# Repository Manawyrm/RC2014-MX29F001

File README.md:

# MX29F001B 128KiB Flash board

PCB tested & working, needs 74HCT32 chip  
Maps 8k of ROM into the start of the address space  
  
Gerbers available in gerber/-Folder

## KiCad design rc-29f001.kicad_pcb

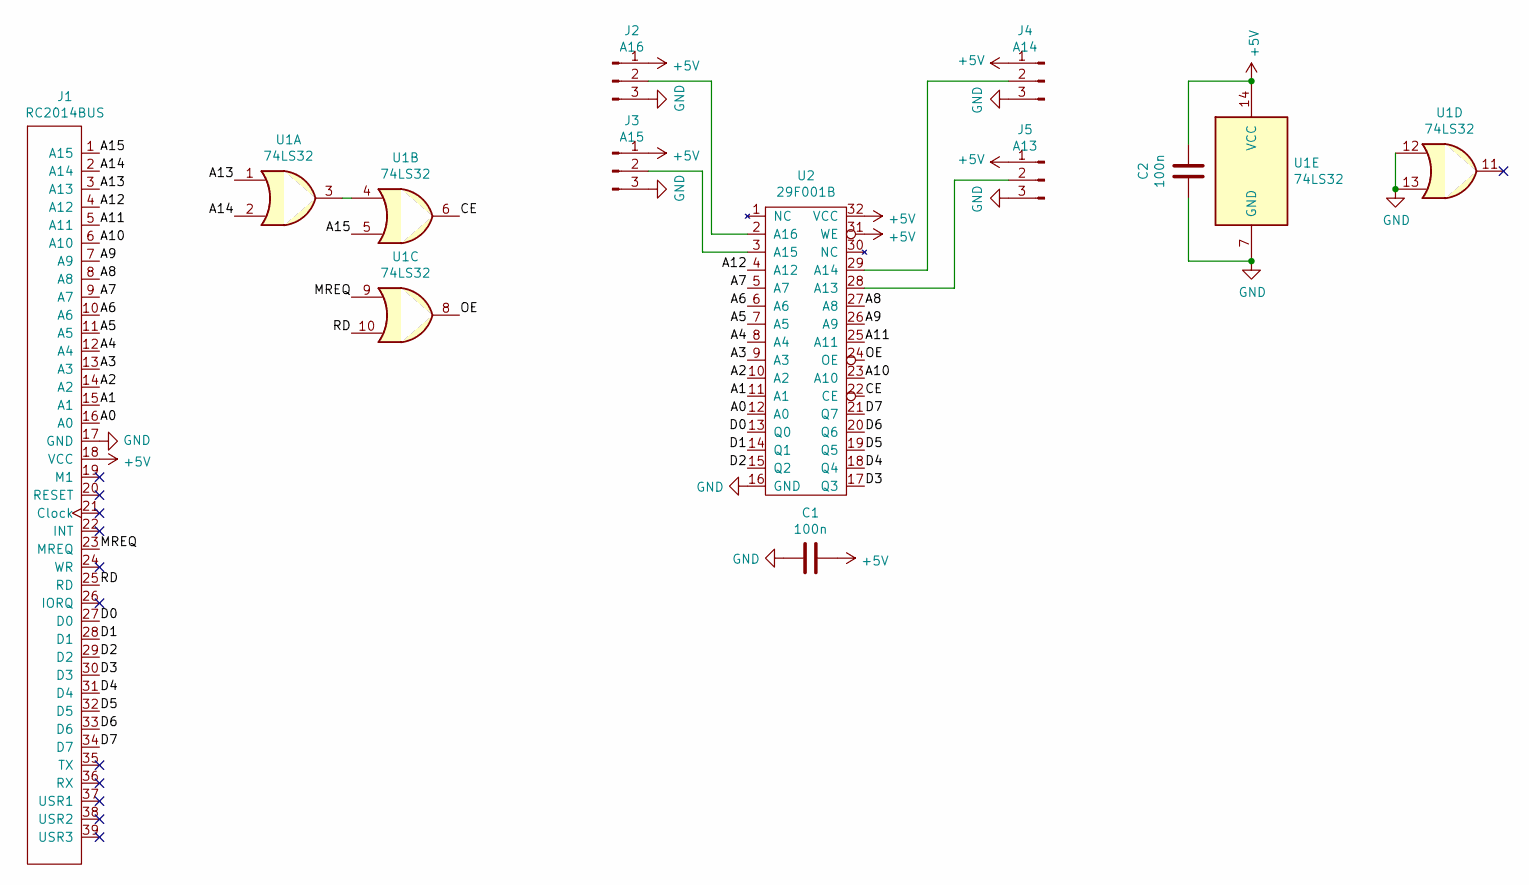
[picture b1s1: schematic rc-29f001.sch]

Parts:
C1, C2: 100n; C_0805_HandSoldering
J1: RC2014BUS; PinHeader_1x39_P2.54mm_Vertical
J2: A16; Pin_Header_Straight_1x03_Pitch2.54mm
J3: A15; Pin_Header_Straight_1x03_Pitch2.54mm
J4: A14; Pin_Header_Straight_1x03_Pitch2.54mm
J5: A13; Pin_Header_Straight_1x03_Pitch2.54mm
U1: 74LS32; DIP-14_W7.62mm_Socket_LongPads
U2: 29F001B; DIP-32_W15.24mm_Socket_LongPads

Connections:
+5V: C1.1, C2.1, J1.18 (VCC), J2.1, J3.1, J4.1, J5.1, U1.14 (VCC), U2.31 (WE), U2.32 (VCC)
/A0: J1.16 (A0), U2.12 (A0)
/A1: J1.15 (A1), U2.11 (A1)
/A2: J1.14 (A2), U2.10 (A2)
/A3: J1.13 (A3), U2.9 (A3)
/A4: J1.12 (A4), U2.8 (A4)
/A5: J1.11 (A5), U2.7 (A5)
/A6: J1.10 (A6), U2.6 (A6)
/A7: J1.9 (A7), U2.5 (A7)
/A8: J1.8 (A8), U2.27 (A8)
/A9: J1.7 (A9), U2.26 (A9)
/A10: J1.6 (A10), U2.23 (A10)
/A11: J1.5 (A11), U2.25 (A11)
/A12: J1.4 (A12), U2.4 (A12)
/A13: J1.3 (A13), U1.1
/A14: J1.2 (A14), U1.2
/A15: J1.1 (A15), U1.5
/CE: U1.6, U2.22 (CE)
/D0: J1.27 (D0), U2.13 (Q0)
/D1: J1.28 (D1), U2.14 (Q1)
/D2: J1.29 (D2), U2.15 (Q2)
/D3: J1.30 (D3), U2.17 (Q3)
/D4: J1.31 (D4), U2.18 (Q4)
/D5: J1.32 (D5), U2.19 (Q5)
/D6: J1.33 (D6), U2.20 (Q6)
/D7: J1.34 (D7), U2.21 (Q7)
/MREQ: J1.23 (MREQ), U1.9
/OE: U1.8, U2.24 (OE)
/RD: J1.25 (RD), U1.10
GND: C1.2, C2.2, J1.17 (GND), J2.3, J3.3, J4.3, J5.3, U1.7 (GND), U1.12, U1.13, U2.16 (GND)
unnamed: J2.2, U2.2 (A16)
unnamed: J3.2, U2.3 (A15)
unnamed: J4.2, U2.29 (A14)
unnamed: J5.2, U2.28 (A13)
unnamed: U1.3, U1.4

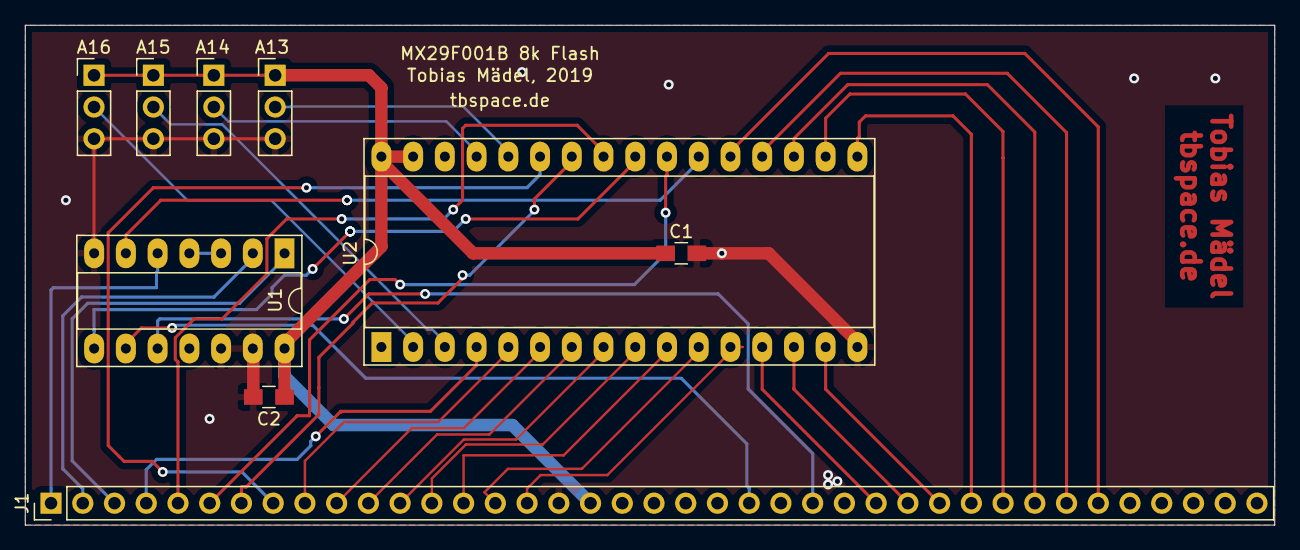
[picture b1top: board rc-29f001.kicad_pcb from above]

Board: 2 copper layers, 100.0 x 40.0 mm, 9 parts (0 on the bottom side), 35 nets.

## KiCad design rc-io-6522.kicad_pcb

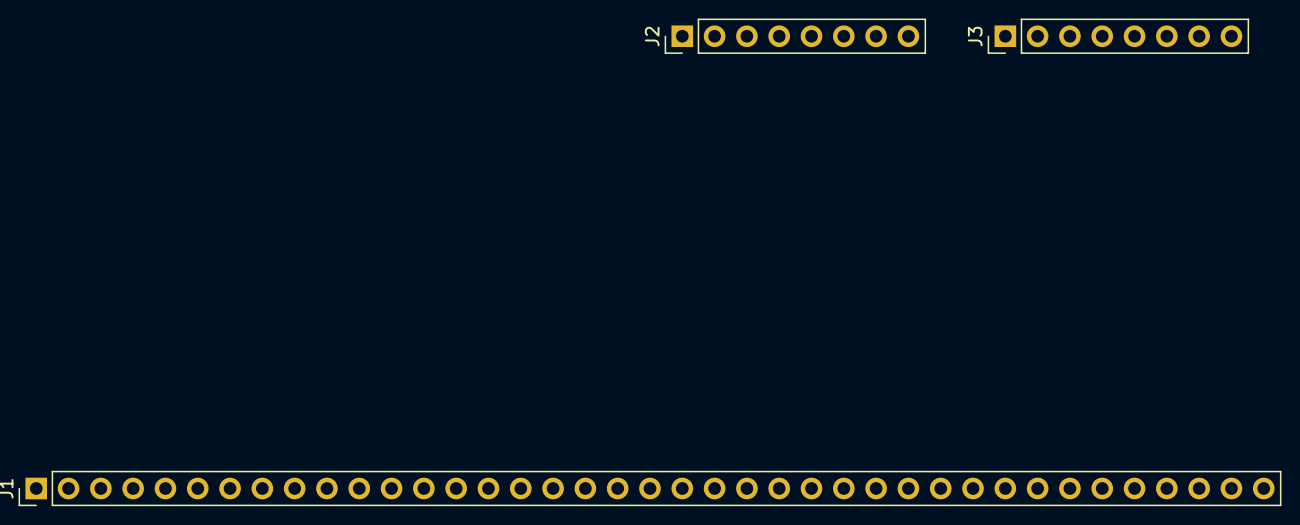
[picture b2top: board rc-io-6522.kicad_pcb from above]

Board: 2 copper layers, 4 parts (1 on the bottom side), 24 nets, no tracks yet.

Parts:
J1: RC2014BUS; PinHeader_1x39_P2.54mm_Vertical
J2, J3: Conn_01x08_Male; PinHeader_1x08_P2.54mm_Vertical
U1: W65C22; TQFP-44_10x10mm_P0.8mm

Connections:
/D0: J1.27, U1.30
/D1: J1.28, U1.29
/D2: J1.29, U1.28
/D3: J1.30, U1.26
/D4: J1.31, U1.25
/D5: J1.32, U1.24
/D6: J1.33, U1.23
/D7: J1.34, U1.22
unnamed: J2.1, U1.40
unnamed: J2.2, U1.41
unnamed: J2.3, U1.42
unnamed: J2.4, U1.43
unnamed: J2.5, U1.44
unnamed: J2.6, U1.1
unnamed: J2.7, U1.2
unnamed: J2.8, U1.3
unnamed: J3.1, U1.4
unnamed: J3.2, U1.6
unnamed: J3.3, U1.7
unnamed: J3.4, U1.8
unnamed: J3.5, U1.9
unnamed: J3.6, U1.10
unnamed: J3.7, U1.11
unnamed: J3.8, U1.12

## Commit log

2019-11-06 Working version
2019-11-06 Create LICENSE
2019-11-06 Added readme
